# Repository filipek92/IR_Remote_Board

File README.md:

View this project on [CADLAB.io](https://cadlab.io/project/1570). 

# IR_Remote_Board

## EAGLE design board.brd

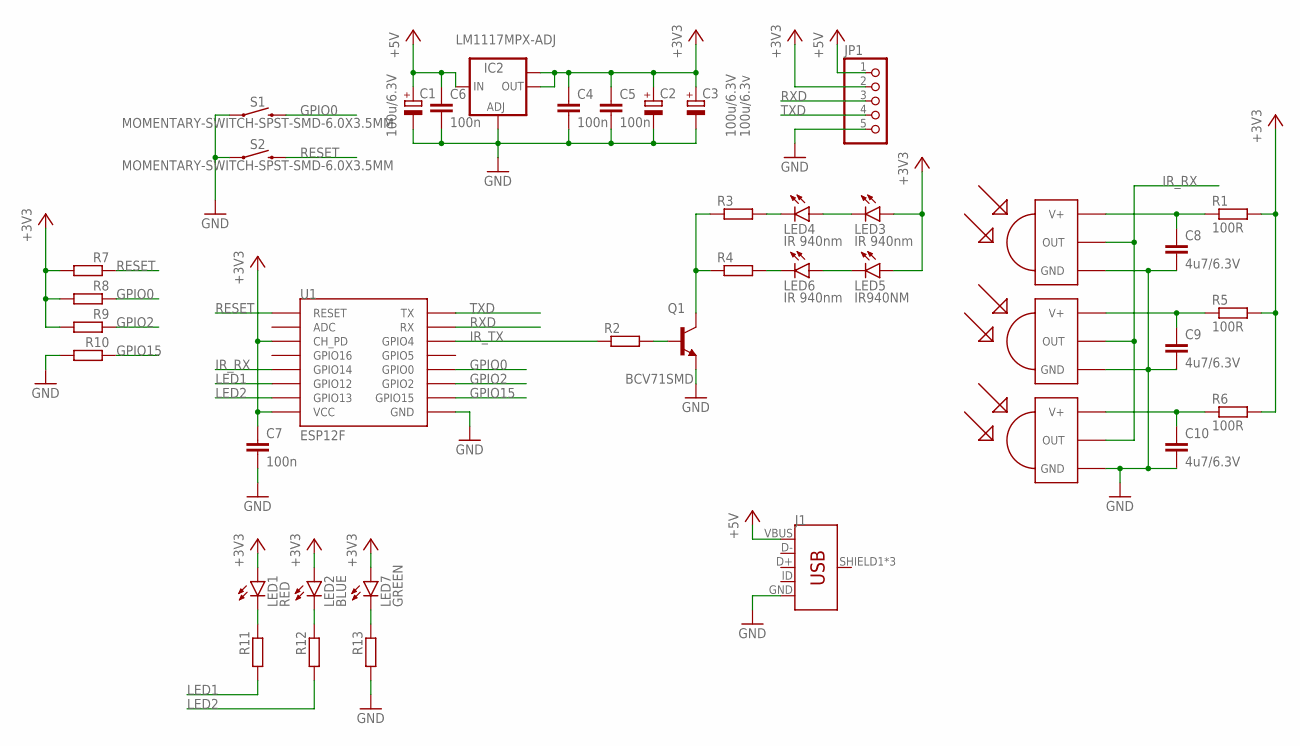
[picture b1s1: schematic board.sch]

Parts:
C1, C2: 100u/6.3V; 153CLV-0605
C3: 100u/6.3v; 153CLV-0605
C4, C5, C6, C7: 100n; C0805
C8, C9, C10: 4u7/6.3V; C0805
IC2: LM1117MPX-ADJ; SOT223
J1: USB_MICRO-B_FEMALE-SMT; USB-B-MICRO-SMD
JP1: PINHD-1X5; 1X05
LED1: RED; CHIPLED_0805
LED2: BLUE; CHIPLED_0805
LED3, LED4, LED6: IR 940nm; LED5MM
LED5: IR940NM; LED5MM
LED7: GREEN; CHIPLED_0805
Q1: BCV71SMD; SOT23-BEC
R1, R5, R6: 100R; M0805
R2, R3, R4, R7, R8, R9, R10, R11, R12, R13: R-EU_M0805; M0805
S1, S2: MOMENTARY-SWITCH-SPST-SMD-6.0X3.5MM; TACTILE_SWITCH_SMD_6.0X3.5MM
U1: ESP12F; ESP12-SMD
U$1, U$2, U$3: TSOP4838; TSOP18XX

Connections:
+3V3: C2.+, C3.+, C4.1, C5.1, C7.1, IC2.2 (OUT), IC2.TAB (OUT1), JP1.2, LED1.A, LED2.A, LED3.A, LED5.A, LED7.A, R1.2, R5.2, R6.2, R7.2, R8.2, R9.2, U1.CH_PD, U1.VCC
+5V: C1.+, C6.1, IC2.3 (IN), J1.VBUS, JP1.1
GND: C1.-, C2.-, C3.-, C4.2, C5.2, C6.2, C7.2, C8.2, C9.2, C10.2, IC2.1 (ADJ), J1.GND, JP1.5, Q1.E, R10.2, R13.2, S1.1, S2.1, U1.GND, U$1.GND, U$2.GND, U$3.GND
GPIO0: R8.1, S1.2, U1.GPIO0
GPIO2: R9.1, U1.GPIO2
GPIO15: R10.1, U1.GPIO15
IR_RX: U1.GPIO14, U$1.OUT, U$2.OUT, U$3.OUT
IR_TX: R2.1, U1.GPIO4
LED1: R11.2, U1.GPIO12
LED2: R12.2, U1.GPIO13
unnamed: LED3.K (C), LED4.A
unnamed: LED5.K (C), LED6.A
unnamed: C9.1, R5.1, U$2.VCC (V+)
unnamed: C8.1, R1.1, U$1.VCC (V+)
unnamed: Q1.C, R3.1, R4.1
unnamed: C10.1, R6.1, U$3.VCC (V+)
unnamed: LED7.C, R13.1
unnamed: Q1.B, R2.2
unnamed: LED2.C, R12.1
unnamed: LED4.K (C), R3.2
unnamed: LED6.K (C), R4.2
unnamed: LED1.C, R11.1
RESET: R7.1, S2.2, U1.RESET
RXD: JP1.3, U1.RXD0 (RX)
TXD: JP1.4, U1.TXD0 (TX)

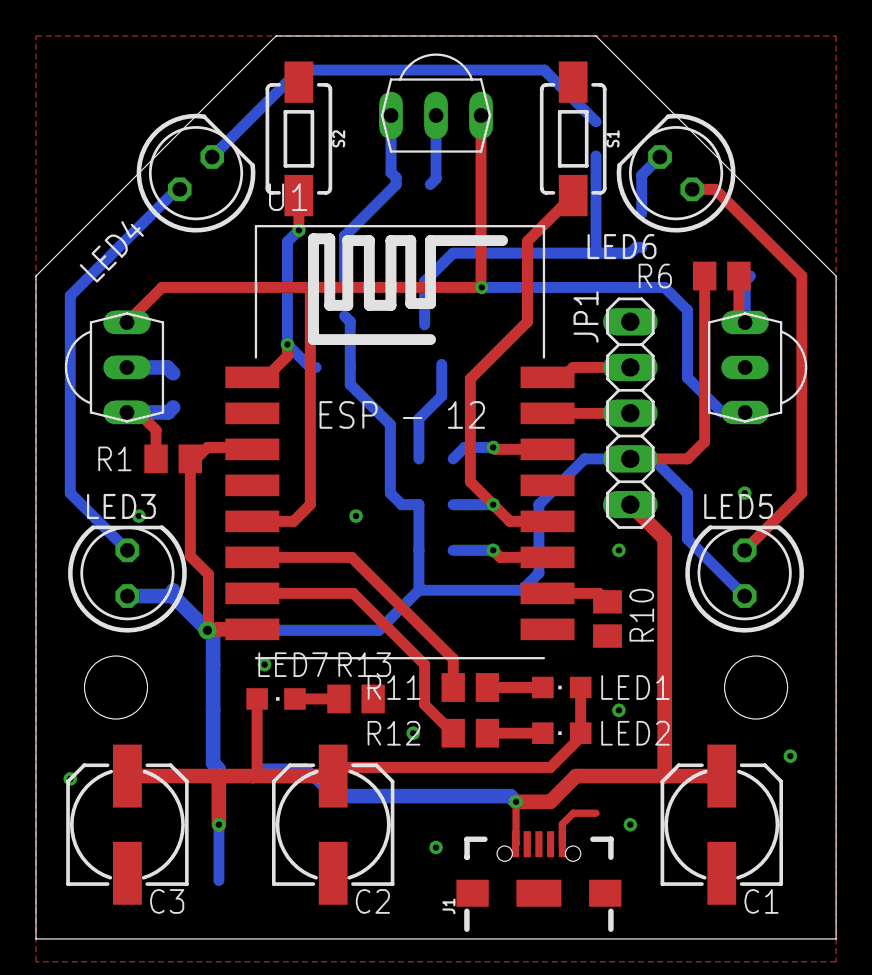
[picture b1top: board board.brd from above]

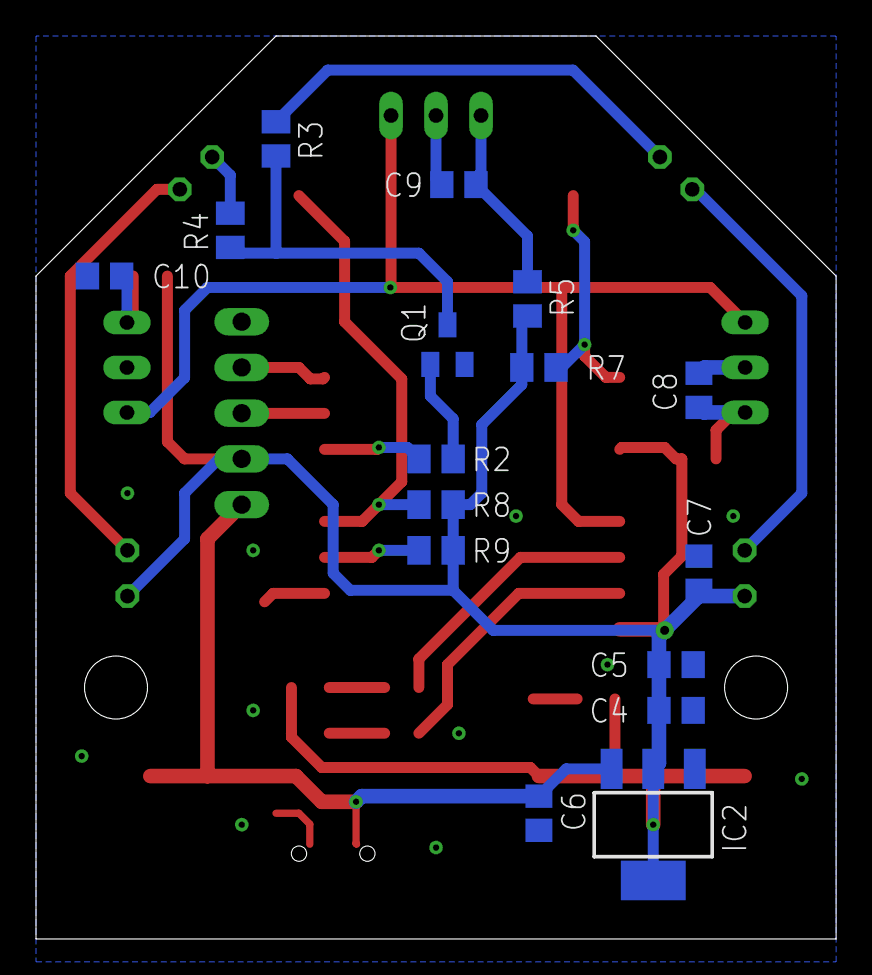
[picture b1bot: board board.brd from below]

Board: 2 copper layers, 44.5 x 50.2 mm, 40 parts (16 on the bottom side), 25 nets.

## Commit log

2019-01-20 First version
2019-01-20 Backlink to CADLAB.io has been added.

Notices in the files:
parts and their libraries:
SparkFun-Connectors: Licensing: Creative Commons ShareAlike 4.0 International - https://creativecommons.org/licenses/by-sa/4.0
